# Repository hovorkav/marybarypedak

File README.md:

# marybarypedak
pedak
## zdroje
schema - https://beavisaudio.com/projects/colorsoundwah/

model - https://www.instructables.com/DIY-Wah-Pedal/
## Dily
*sem to dopis honzo*

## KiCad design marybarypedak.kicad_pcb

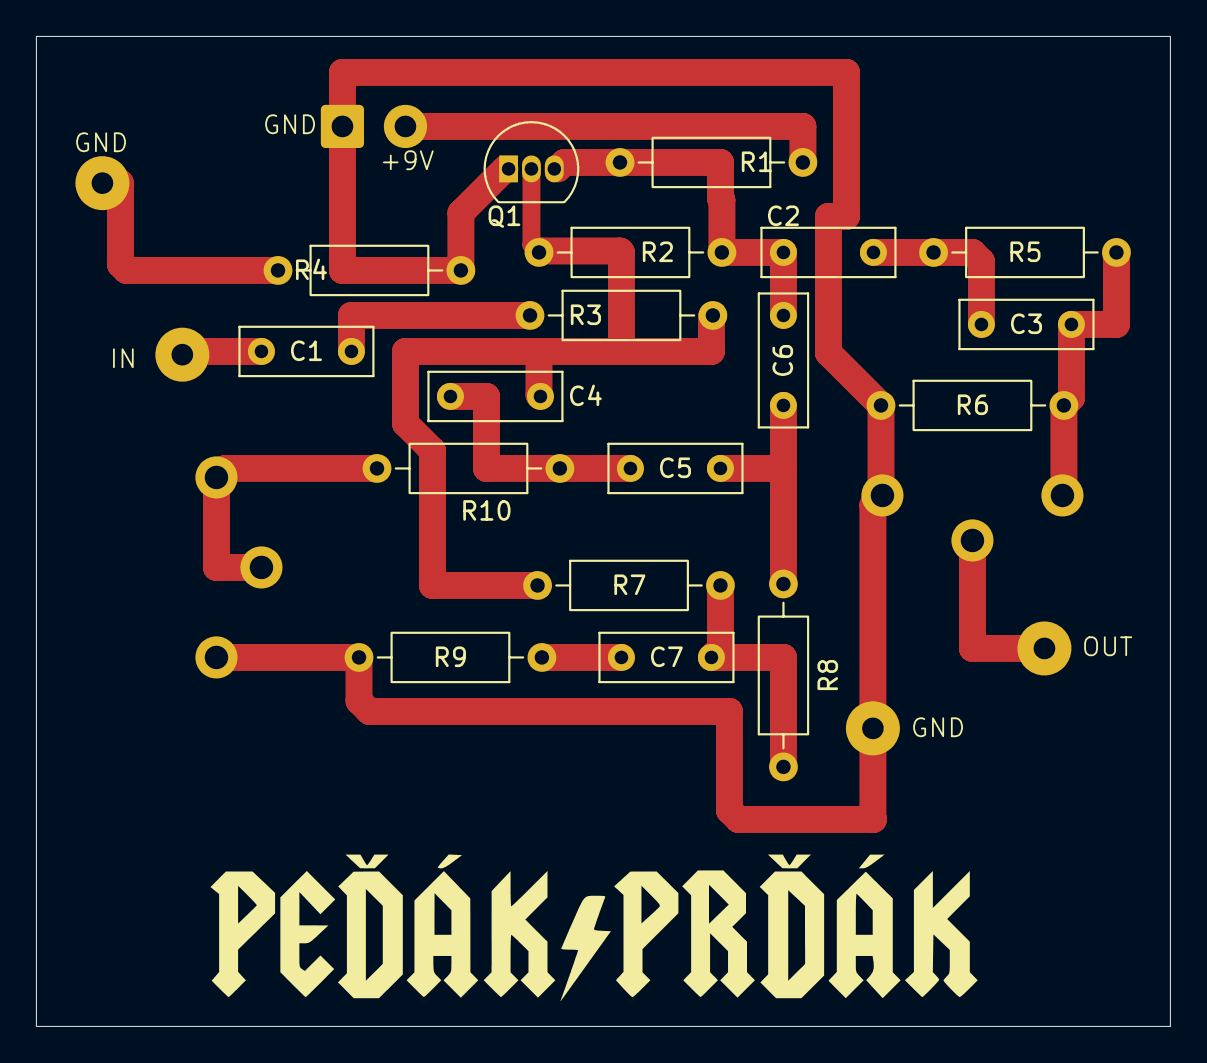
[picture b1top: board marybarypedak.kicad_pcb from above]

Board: 2 copper layers, 63.0 x 55.0 mm, 23 parts (0 on the bottom side), 15 nets.

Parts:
C1, C2, C6, C7: 100nF; C_Rect_L7.2mm_W2.5mm_P5.00mm
C3, C4, C5: 2.2nF; C_Rect_L7.2mm_W2.5mm_P5.00mm
J1, J2: NJ2FD-V; Jack_speakON_Neutrik_NL2MDXX-H-3_Horizontal
J3: Conn_01x02_Socket; TerminalBlock_4Ucon_1x02_P3.50mm_Horizontal
Q1: 2N3904; TO-92_Inline
R1, R5: 10k; R_Axial_DIN0207_L6.3mm_D2.5mm_P10.16mm_Horizontal
R2: 5M7; R_Axial_DIN0207_L6.3mm_D2.5mm_P10.16mm_Horizontal
R3: 330k; R_Axial_DIN0207_L6.3mm_D2.5mm_P10.16mm_Horizontal
R4: 1M; R_Axial_DIN0207_L6.3mm_D2.5mm_P10.16mm_Horizontal
R6: 47k; R_Axial_DIN0207_L6.3mm_D2.5mm_P10.16mm_Horizontal
R7, R8: 180k; R_Axial_DIN0207_L6.3mm_D2.5mm_P10.16mm_Horizontal
R9, R10: 33k; R_Axial_DIN0207_L6.3mm_D2.5mm_P10.16mm_Horizontal
RV1: A100k; Potentiometer_ACP_CA14-H2,5_Horizontal
RV2: B100k; Potentiometer_ACP_CA14-H2,5_Horizontal

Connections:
+9V: J3.2, R1.1
GND: J2.1-, J3.1, Q1.1 (E), R4.2, R6.1, R9.2, RV1.3, RV2.3
unnamed: C1.1, J1.1+
unnamed: C1.2, R3.1
unnamed: C2.2, C3.1, R5.1
unnamed: C3.2, R5.2, R6.2, RV1.1
unnamed: C4.2, C5.1, R10.1
unnamed: C5.2, C6.1, R8.2
unnamed: C7.1, R9.1
unnamed: C7.2, R7.2, R8.1
unnamed: J1.1-, R4.1
unnamed: J2.1+, RV1.2
unnamed: C4.1, Q1.2 (B), R2.1, R3.2, R7.1
unnamed: C2.1, C6.2, Q1.3 (C), R1.2, R2.2
unnamed: R10.2, RV2.1, RV2.2

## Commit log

2026-06-16 Schema design, repo innit
2026-06-16 Add resources and sections to README
2026-06-19 Sranda, pridani e-shop odkazu
2026-06-20 PCB, gerber
